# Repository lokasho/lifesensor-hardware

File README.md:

# lifesensor-hardware
Temporary repository for the next hardware generation of the CADUS Life Sensor.
Official repository at https://github.com/cadus/Life-Sensor.

## Similar projects and Resources:
- https://github.com/GliaX
- https://github.com/kitspace/awesome-electronics
- https://github.com/kitspace/kicad_footprints
- https://github.com/intajay/open-electronics

- ecg
    + https://github.com/xdever/MobilECG-II -> based on ADS1298
    + https://www.olimex.com/Products/Duino/Shields/SHIELD-EKG-EMG/open-source-hardware
    + https://www.electronicdesign.com/power-management/article/21798161/choose-the-right-resistors-for-medical-applications

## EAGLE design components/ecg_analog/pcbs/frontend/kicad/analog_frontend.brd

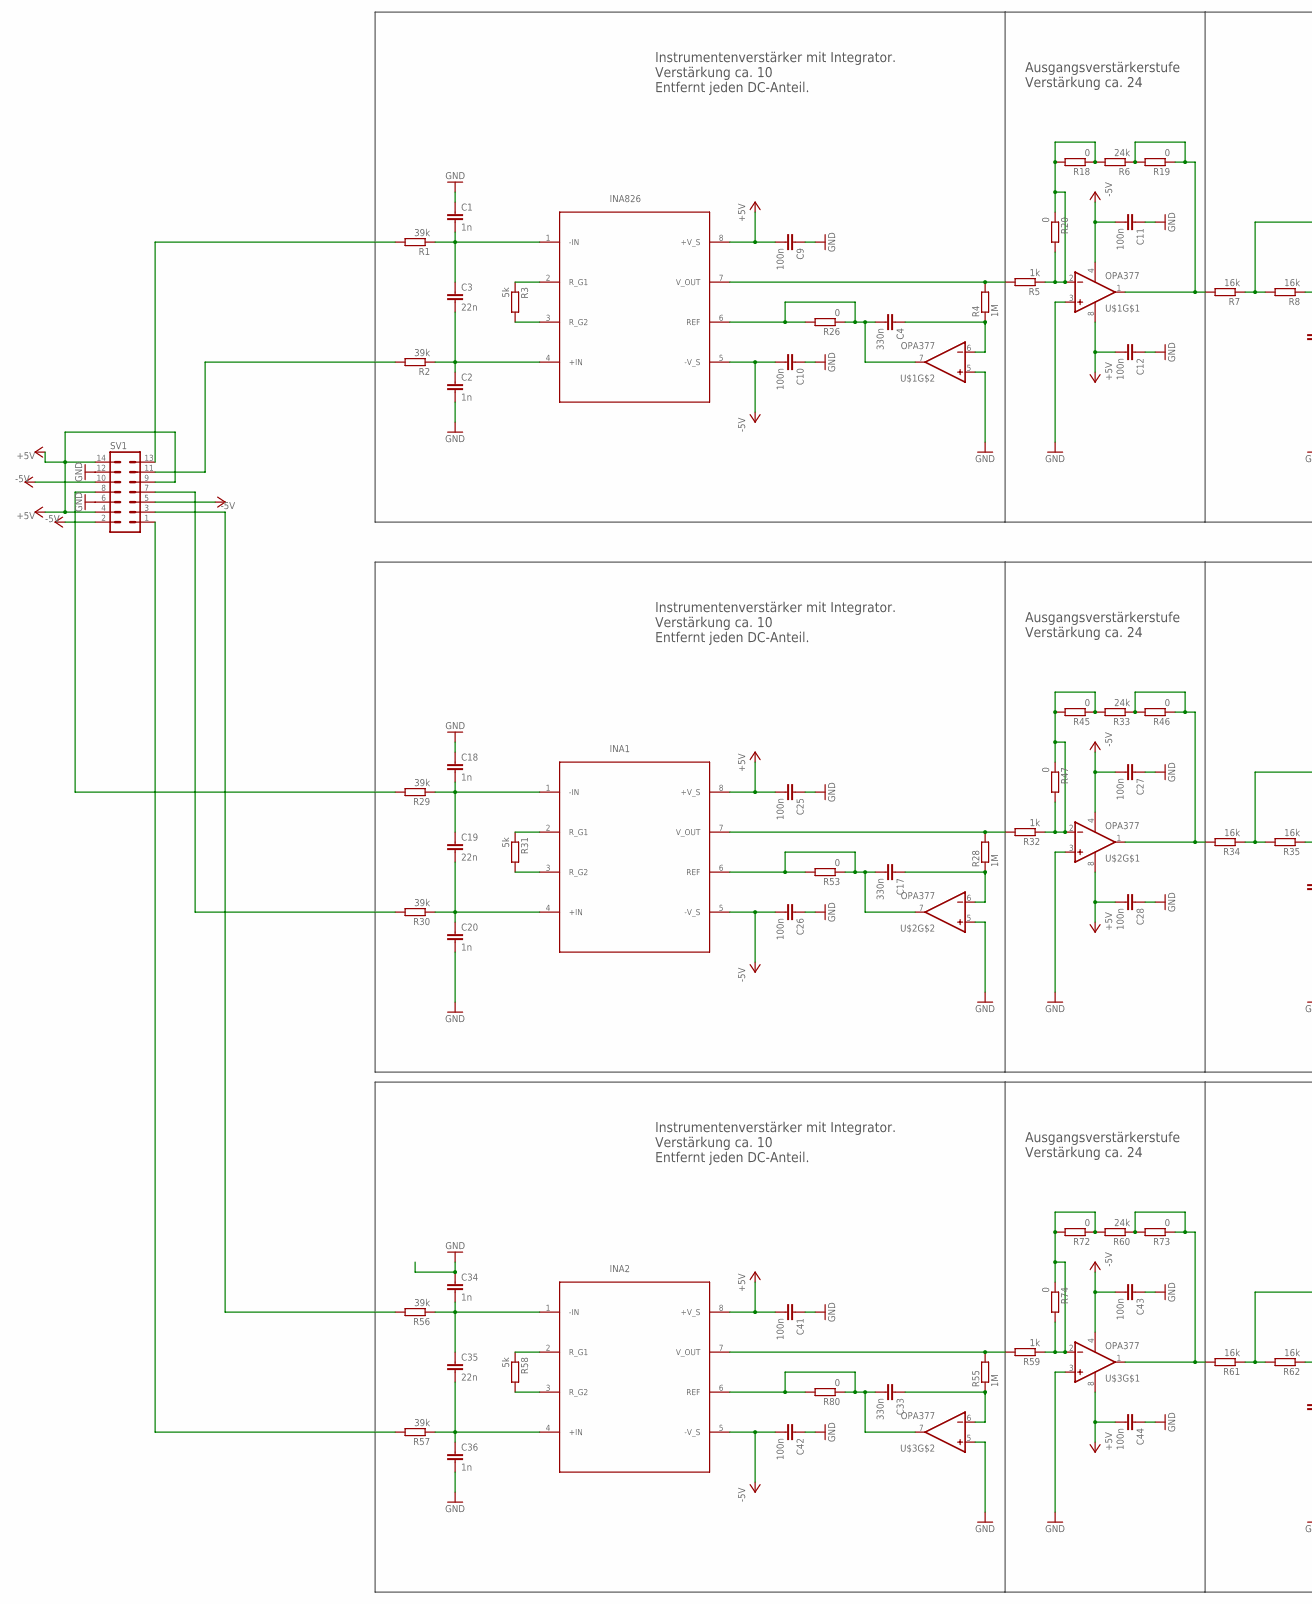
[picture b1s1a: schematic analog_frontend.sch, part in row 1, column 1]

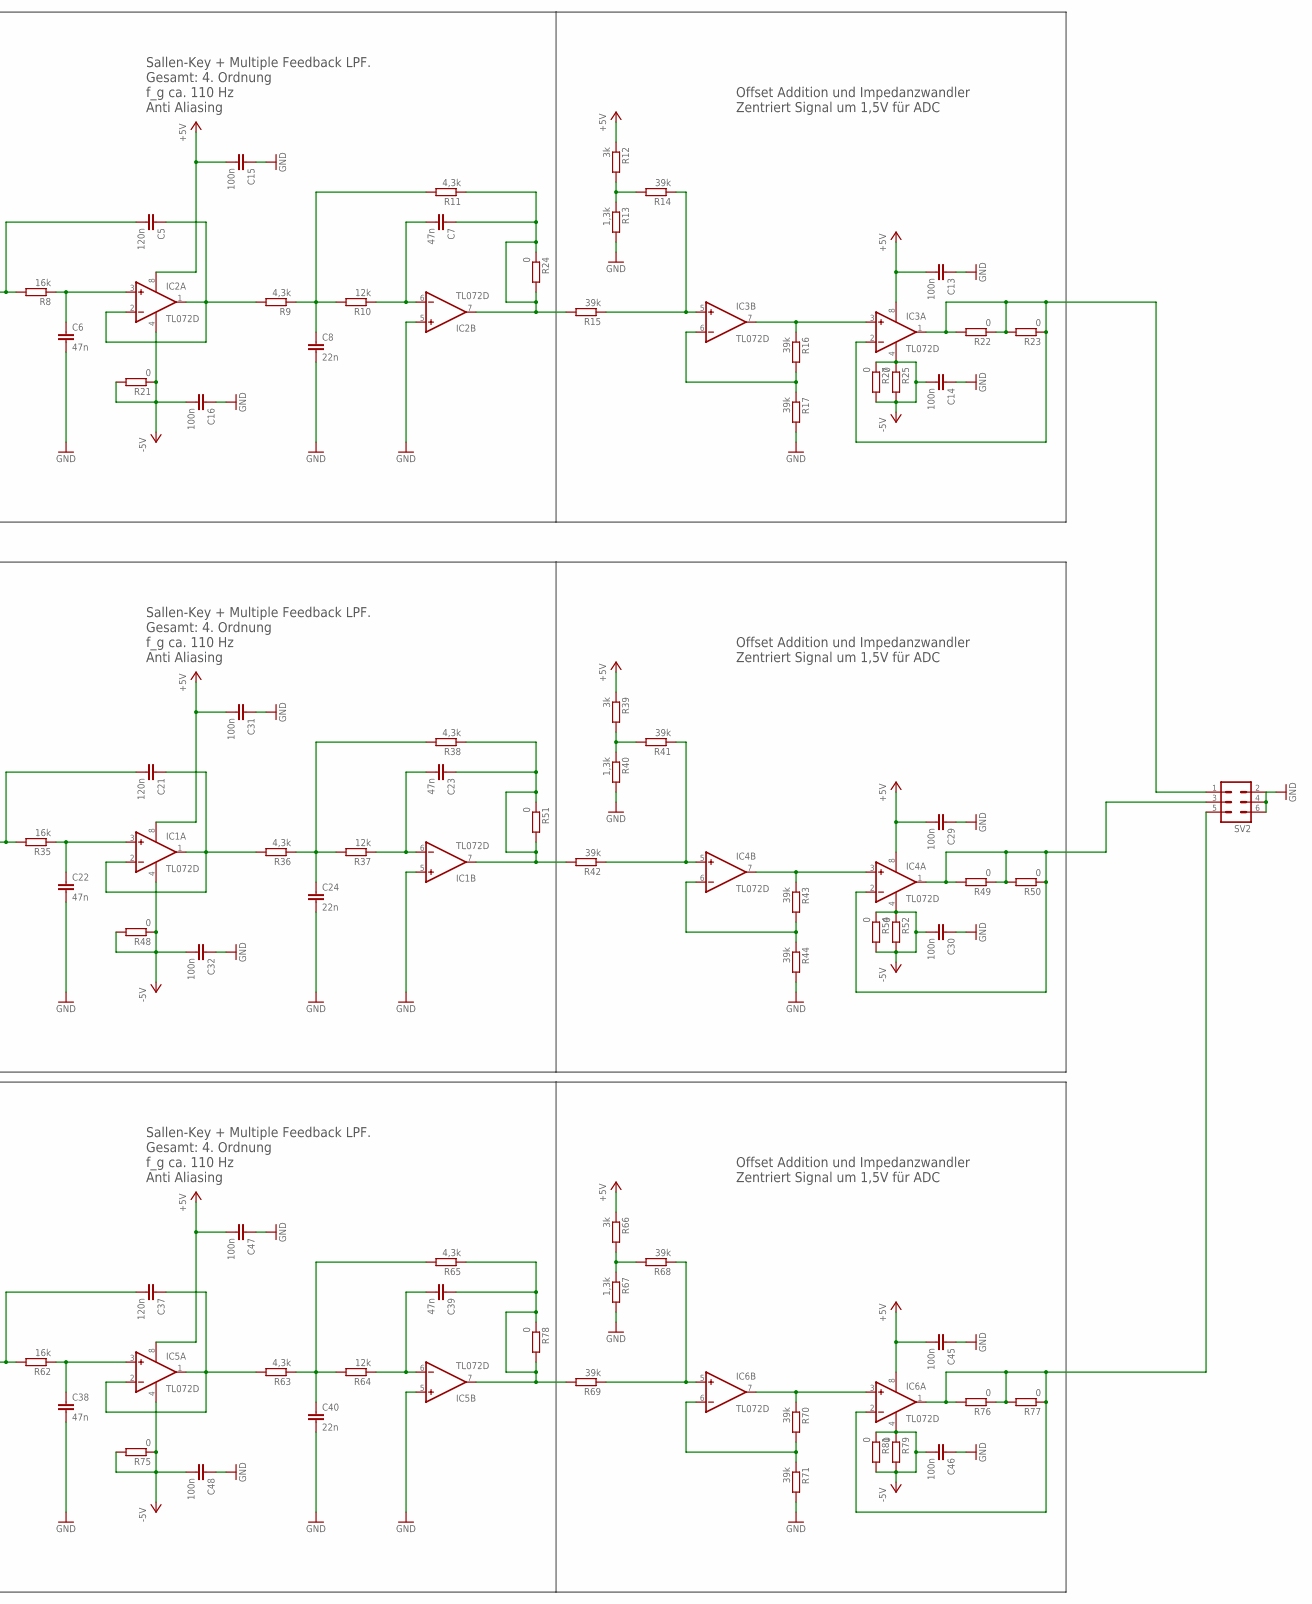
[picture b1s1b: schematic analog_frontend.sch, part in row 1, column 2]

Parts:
C1, C2, C18, C20, C34, C36: 1n; C0805
C3, C8, C19, C24, C35, C40: 22n; C0805
C4, C17, C33: 330n; C1206
C5, C21, C37: 120n; C0805
C6, C7, C22, C23, C38, C39: 47n; C0805
C9, C10, C11, C12, C13, C14, C16, C25, C26, C27, C28, C29, C30, C32, C41, C42, C43, C44, C45, C46, C48: 100n; C0805
C15, C31, C47: 100n; C1206
IC1, IC2, IC3, IC4, IC5, IC6: TL072D; SO08
INA1, INA2, INA826: INA826; SOIC8
R1, R2, R14, R15, R16, R29, R30, R41, R42, R43, R56, R57, R68, R69, R70: 39k; R0805
R3, R31, R58: 5k; R0805
R4, R28, R55: 1M; R1206
R5, R32, R59: 1k; R1206
R6, R33, R60: 24k; R0805
R7, R34, R61: 16k; R1206
R8, R35, R62: 16k; R0805
R9, R11, R36, R38, R63, R65: 4,3k; R0805
R10, R37, R64: 12k; R0805
R12, R39, R66: 3k; R0805
R13, R40, R67: 1,3k; R1206
R17, R44, R71: 39k; R1206
R18, R19, R20, R21, R22, R23, R24, R25, R26, R27, R45, R46, R47, R48, R49, R50, R51, R52, R53, R54, R72, R73, R74, R75, R76, R77, R78, R79, R80, R81: 0; R1206
SV1: ML14L
SV2: ML6L
U$1, U$2, U$3: OPA377; SOIC8

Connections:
+5V: C9.2, C12.2, C13.2, C15.2, C25.2, C28.2, C29.2, C31.2, C41.2, C44.2, C45.2, C47.2, IC1.8 (V+), IC2.8 (V+), IC3.8 (V+), IC4.8 (V+), IC5.8 (V+), IC6.8 (V+), INA1.8 (+V_S), INA2.8 (+V_S), INA826.8 (+V_S), R12.1, R39.1, R66.1, SV1.4, SV1.9, SV1.14, U$1.8 (V+), U$2.8 (V+), U$3.8 (V+)
-5V: C10.2, C11.2, C14.2, C16.2, C26.2, C27.2, C30.2, C32.2, C42.2, C43.2, C46.2, C48.2, IC1.4 (V-), IC2.4 (V-), IC3.4 (V-), IC4.4 (V-), IC5.4 (V-), IC6.4 (V-), INA1.5 (-V_S), INA2.5 (-V_S), INA826.5 (-V_S), R21.1, R21.2, R25.1, R25.2, R27.1, R27.2, R48.1, R48.2, R52.1, R52.2, R54.1, R54.2, R75.1, R75.2, R79.1, R79.2, R81.1, R81.2, SV1.2, SV1.5, SV1.10, U$1.4 (V-), U$2.4 (V-), U$3.4 (V-)
GND: C1.1, C2.2, C6.2, C8.2, C9.1, C10.1, C11.1, C12.1, C13.1, C14.1, C15.1, C16.1, C18.1, C20.2, C22.2, C24.2, C25.1, C26.1, C27.1, C28.1, C29.1, C30.1, C31.1, C32.1, C34.1, C36.2, C38.2, C40.2, C41.1, C42.1, C43.1, C44.1, C45.1, C46.1, C47.1, C48.1, IC1.5 (+IN), IC2.5 (+IN), IC5.5 (+IN), R13.2, R17.2, R40.2, R44.2, R67.2, R71.2, SV1.6, SV1.12, SV2.2, SV2.4, SV2.6, U$1.3 (+IN), U$1.5 (+IN), U$2.3 (+IN), U$2.5 (+IN), U$3.3 (+IN), U$3.5 (+IN)
unnamed: C4.2, INA826.6 (REF), R26.1, R26.2, U$1.7 (OUT)
unnamed: C4.1, R4.1, U$1.6 (-IN)
unnamed: INA826.7 (V_OUT), R4.2, R5.2
unnamed: C1.2, C3.1, INA826.1 (-IN), R1.1
unnamed: C2.1, C3.2, INA826.4 (+IN), R2.1
unnamed: INA826.3 (R_G2), R3.2
unnamed: INA826.2 (R_G1), R3.1
unnamed: R5.1, R6.2, R18.1, R18.2, R20.1, R20.2, U$1.2 (-IN)
unnamed: R6.1, R7.2, R19.1, R19.2, U$1.1 (OUT)
unnamed: C5.2, R7.1, R8.2
unnamed: C5.1, IC2.1 (OUT), IC2.2 (-IN), R9.2
unnamed: C6.1, IC2.3 (+IN), R8.1
unnamed: C8.1, R9.1, R10.2, R11.2
unnamed: C7.2, IC2.6 (-IN), R10.1
unnamed: C7.1, IC2.7 (OUT), R11.1, R15.2, R24.1, R24.2
unnamed: IC3.5 (+IN), R14.1, R15.1
unnamed: IC3.6 (-IN), R16.2, R17.1
unnamed: R12.2, R13.1, R14.2
unnamed: IC3.3 (+IN), IC3.7 (OUT), R16.1
unnamed: IC3.1 (OUT), IC3.2 (-IN), R22.1, R22.2, R23.1, R23.2, SV2.1
unnamed: R1.2, SV1.13
unnamed: R2.2, SV1.11
unnamed: INA1.7 (V_OUT), R28.2, R32.2
unnamed: C17.1, R28.1, U$2.6 (-IN)
unnamed: C18.2, C19.1, INA1.1 (-IN), R29.1
unnamed: C19.2, C20.1, INA1.4 (+IN), R30.1
unnamed: INA1.3 (R_G2), R31.2
unnamed: INA1.2 (R_G1), R31.1
unnamed: C21.2, R34.1, R35.2
unnamed: C21.1, IC1.1 (OUT), IC1.2 (-IN), R36.2
unnamed: C22.1, IC1.3 (+IN), R35.1
unnamed: C24.1, R36.1, R37.2, R38.2
unnamed: C23.2, IC1.6 (-IN), R37.1
unnamed: C23.1, IC1.7 (OUT), R38.1, R42.2, R51.1, R51.2
unnamed: IC4.5 (+IN), R41.1, R42.1
unnamed: R39.2, R40.1, R41.2
unnamed: IC4.3 (+IN), IC4.7 (OUT), R43.1
unnamed: IC4.6 (-IN), R43.2, R44.1
unnamed: R32.1, R33.2, R45.1, R45.2, R47.1, R47.2, U$2.2 (-IN)
unnamed: IC4.1 (OUT), IC4.2 (-IN), R49.1, R49.2, R50.1, R50.2, SV2.3
unnamed: C17.2, INA1.6 (REF), R53.1, R53.2, U$2.7 (OUT)
unnamed: R33.1, R34.2, R46.1, R46.2, U$2.1 (OUT)
unnamed: R29.2, SV1.8
unnamed: R30.2, SV1.7
unnamed: INA2.7 (V_OUT), R55.2, R59.2
unnamed: C33.1, R55.1, U$3.6 (-IN)
unnamed: C34.2, C35.1, INA2.1 (-IN), R56.1
unnamed: C35.2, C36.1, INA2.4 (+IN), R57.1
unnamed: INA2.3 (R_G2), R58.2
unnamed: INA2.2 (R_G1), R58.1
unnamed: C37.2, R61.1, R62.2
unnamed: C37.1, IC5.1 (OUT), IC5.2 (-IN), R63.2
unnamed: C38.1, IC5.3 (+IN), R62.1
unnamed: C40.1, R63.1, R64.2, R65.2
unnamed: C39.2, IC5.6 (-IN), R64.1
unnamed: C39.1, IC5.7 (OUT), R65.1, R69.2, R78.1, R78.2
unnamed: IC6.5 (+IN), R68.1, R69.1
unnamed: R66.2, R67.1, R68.2
unnamed: IC6.3 (+IN), IC6.7 (OUT), R70.1
unnamed: IC6.6 (-IN), R70.2, R71.1
unnamed: R59.1, R60.2, R72.1, R72.2, R74.1, R74.2, U$3.2 (-IN)
unnamed: IC6.1 (OUT), IC6.2 (-IN), R76.1, R76.2, R77.1, R77.2, SV2.5
unnamed: C33.2, INA2.6 (REF), R80.1, R80.2, U$3.7 (OUT)
unnamed: R60.1, R61.2, R73.1, R73.2, U$3.1 (OUT)
unnamed: R56.2, SV1.3
unnamed: R57.2, SV1.1

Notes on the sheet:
Instrumentenverstärker mit Integrator. Verstärkung ca. 10 Entfernt jeden DC-Anteil.
Ausgangsverstärkerstufe Verstärkung ca. 24
Sallen-Key + Multiple Feedback LPF. Gesamt: 4. Ordnung f_g ca. 110 Hz Anti Aliasing
Offset Addition und Impedanzwandler Zentriert Signal um 1,5V für ADC

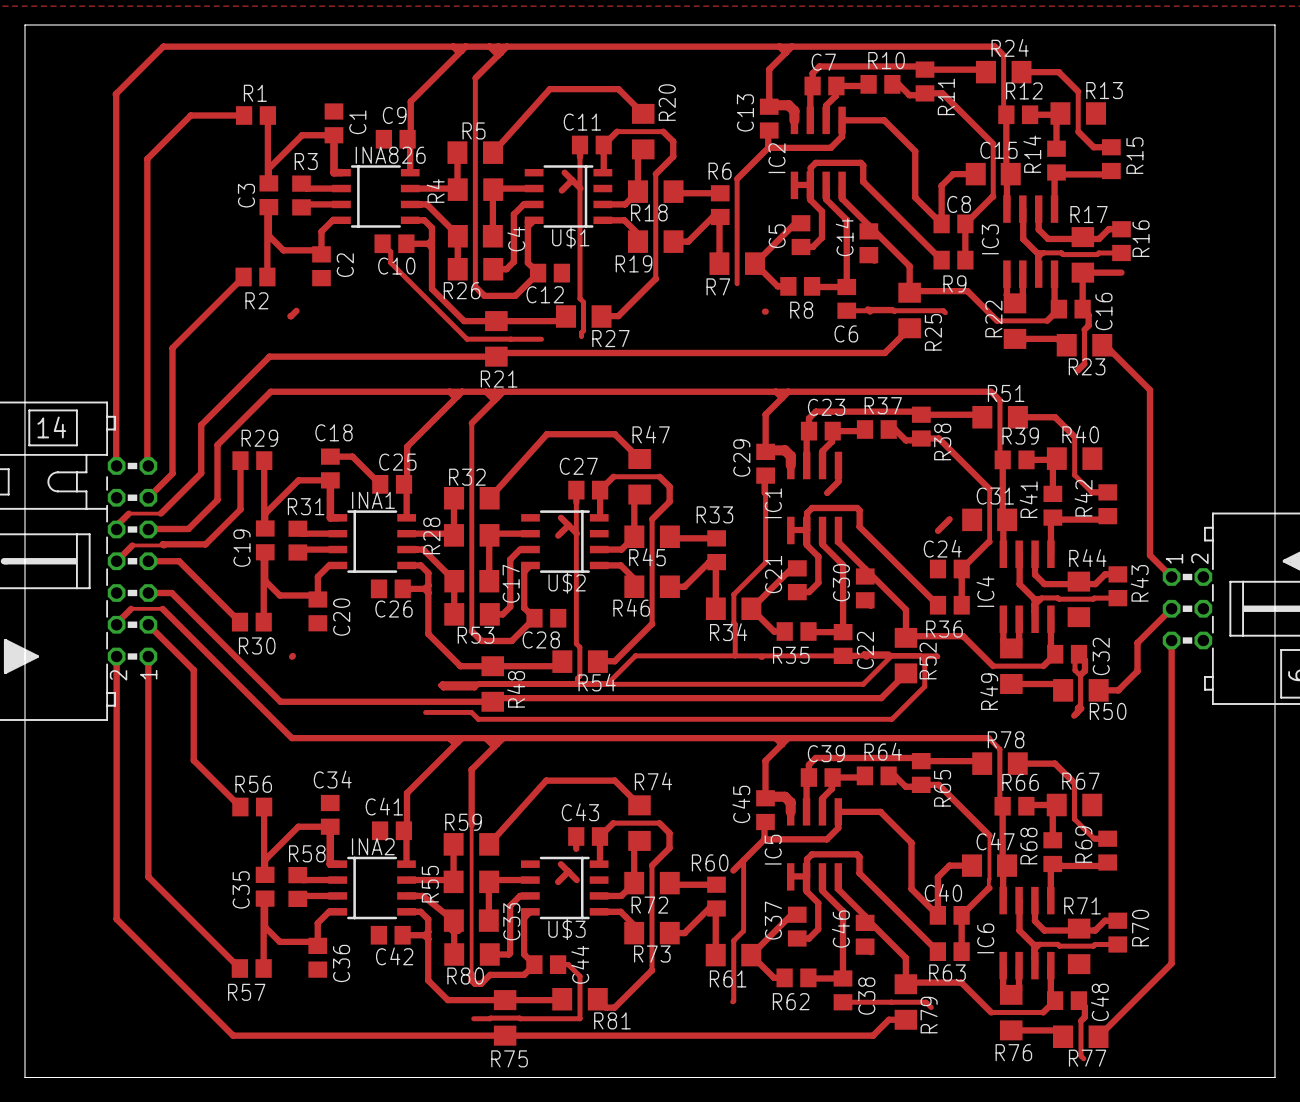
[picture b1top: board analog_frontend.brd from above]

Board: 2 copper layers, 100.0 x 84.2 mm, 143 parts (0 on the bottom side), 69 nets.

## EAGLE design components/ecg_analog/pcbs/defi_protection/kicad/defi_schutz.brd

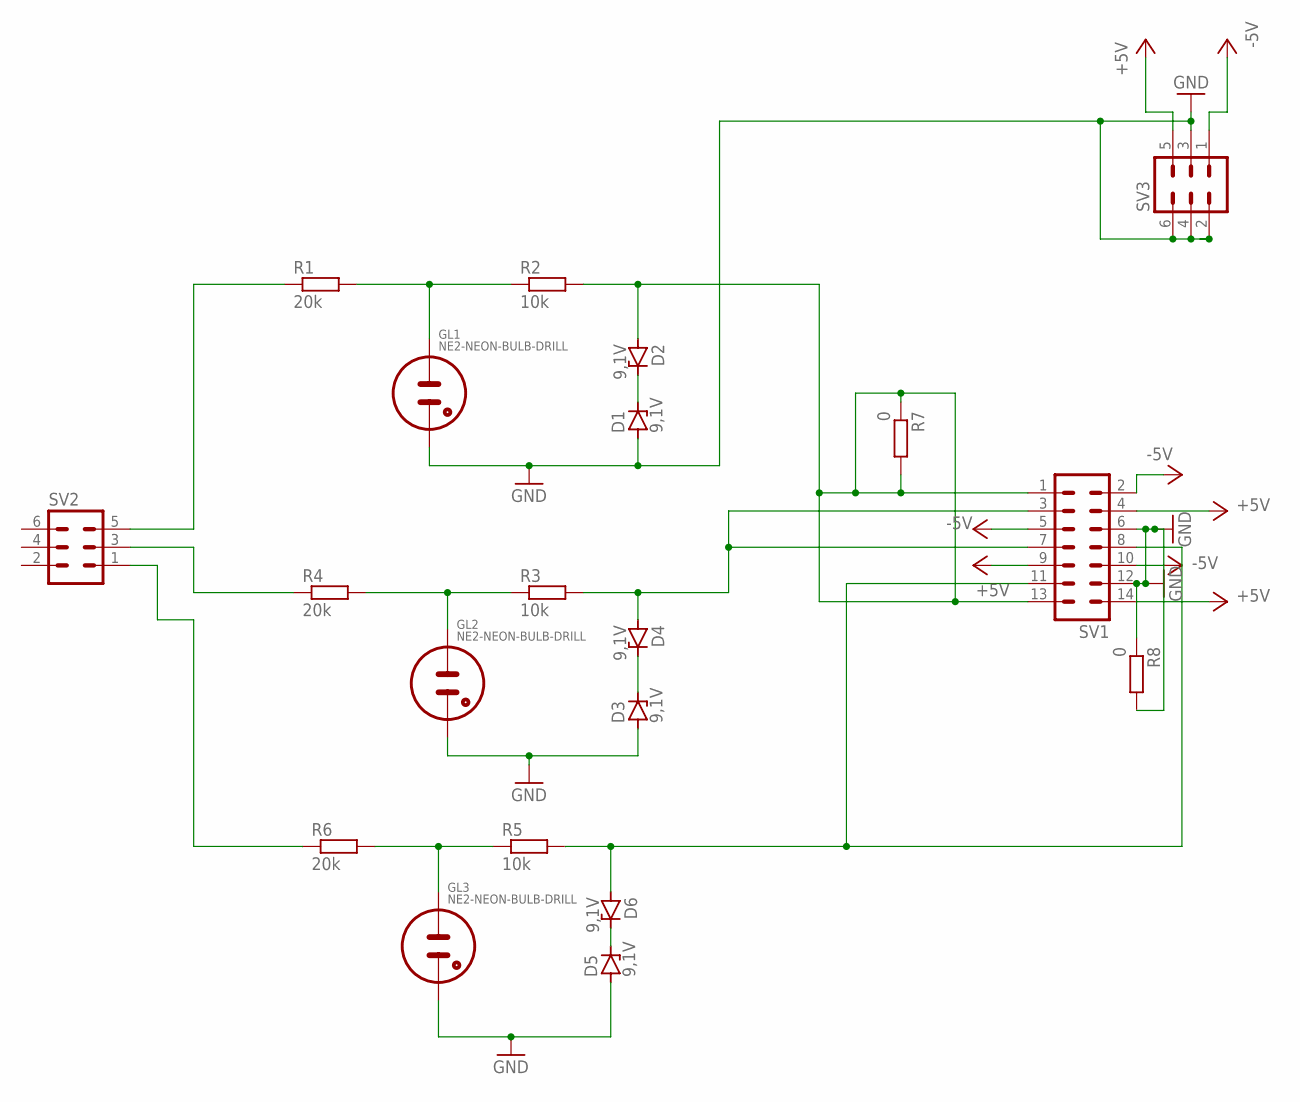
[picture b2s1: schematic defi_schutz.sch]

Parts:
D1, D2, D3, D4, D5, D6: 9,1V; DO41Z10
GL1, GL2, GL3: NE2-NEON-BULB-DRILL
R1, R4, R6: 20k; 0207/10
R2, R3, R5: 10k; 0207/10
R7, R8: 0; 0207/15
SV1: ML14L
SV2, SV3: ML6L

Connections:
+5V: SV1.4, SV1.9, SV1.14, SV3.5
-5V: SV1.2, SV1.5, SV1.10, SV3.1
GND: D1.A, D3.A, D5.A, GL1.2 (A1), GL2.2 (A1), GL3.2 (A1), R8.1, R8.2, SV1.6, SV1.12, SV3.2, SV3.3, SV3.4, SV3.6
unnamed: GL2.1 (A), R3.1, R4.2
unnamed: D4.A, R3.2, SV1.3, SV1.7
unnamed: D3.C, D4.C
unnamed: D1.C, D2.C
unnamed: GL1.1 (A), R1.2, R2.1
unnamed: D2.A, R2.2, R7.1, R7.2, SV1.1, SV1.13
unnamed: GL3.1 (A), R5.1, R6.2
unnamed: D6.A, R5.2, SV1.8, SV1.11
unnamed: D5.C, D6.C
unnamed: R1.1, SV2.5
unnamed: R4.1, SV2.3
unnamed: R6.1, SV2.1

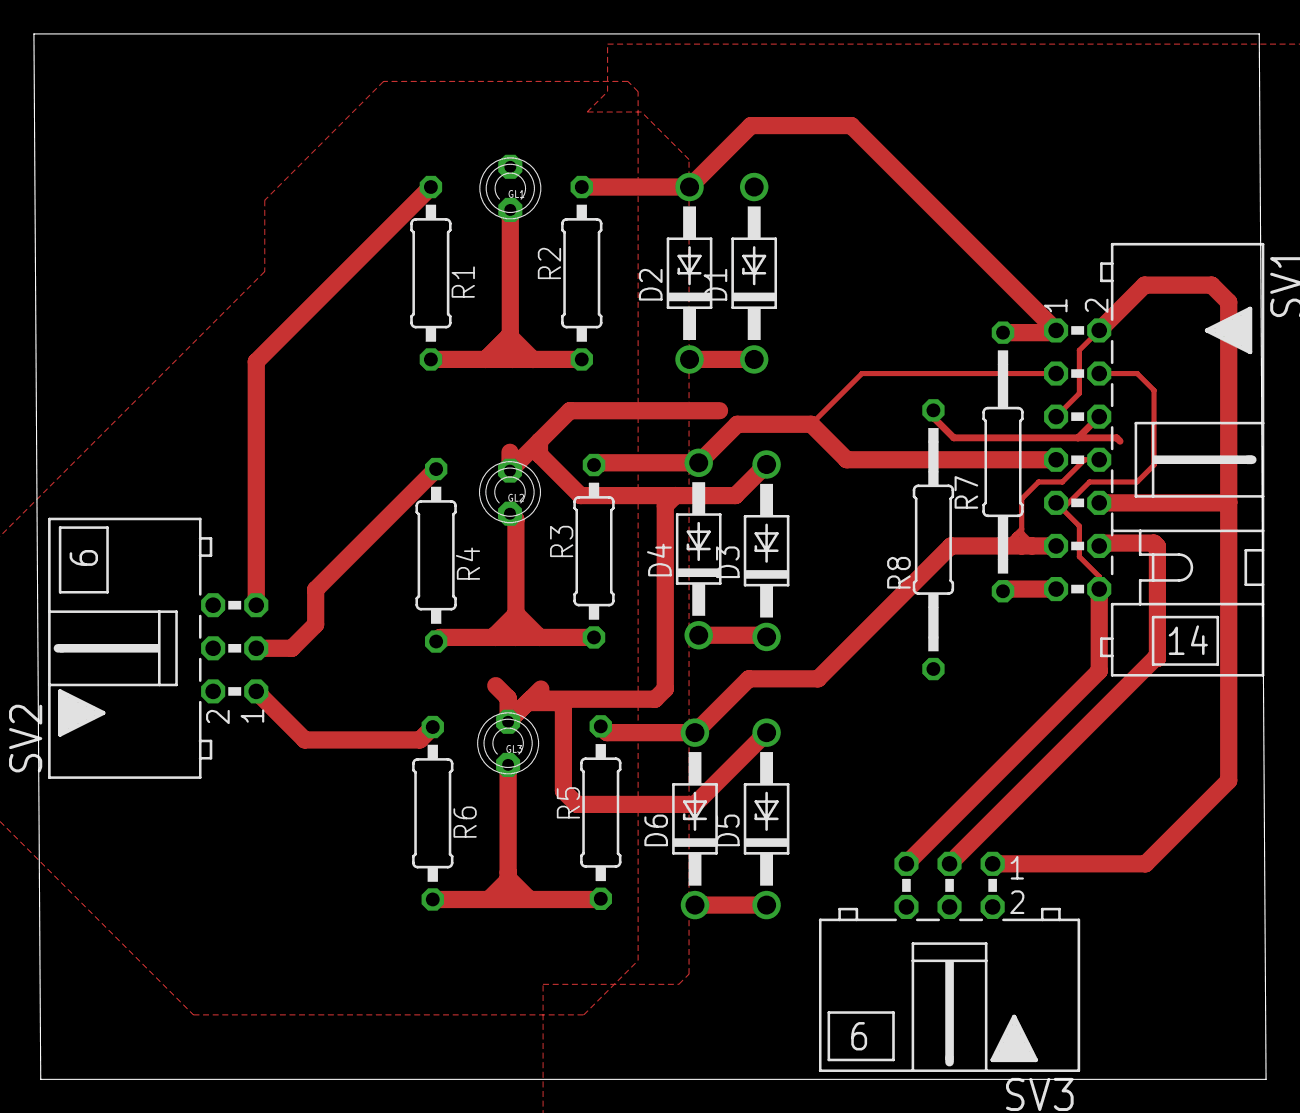
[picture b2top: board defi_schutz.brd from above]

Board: 2 copper layers, 72.6 x 61.6 mm, 20 parts (0 on the bottom side), 15 nets.

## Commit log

2020-03-26 add zenit resources
2020-03-27 update requirements
2020-03-27 add kicad project for ecg
2020-03-28 first draft ecg protection
2020-04-03 update file structure
2020-04-03 include analog frontend
2020-04-03 remove old ecg version
2020-04-03 add dummy ads1292 driver
2020-04-03 add dummy script
2020-04-07 update schematics
2020-04-11 allow daisy chaining and improve ground planes
2020-04-11 fix GND via not connected
2020-04-11 simplify ads1292 supply scheme in schematic
2020-04-15 orientation of pin headers in schematic matches pcb
2020-04-15 add gnd/gndpwr bridge at analog power supply
2020-04-15 add ERC log with allowed warnings
2020-04-15 add board name and version to pcb
2020-04-15 add version and titles to schematic pages
2020-04-22 first sim test with ne2 lib, blanks in sheet name removed
2020-04-25 updates simulation, adds diode, updates voltage source
2020-04-25 add system overview and pcb stack dimensions
2020-04-26 add templates for components and pcbs
2020-04-26 remove obsolete files
2020-04-26 allow scripts to be run from another working dir
2020-04-26 ignore python cache directories
2020-04-27 adds new tvs diode spice models
2020-04-27 new ecg_ads1292 version based on template
2020-04-27 update diode modell
2020-04-27 schematic passes erc with two accpted warnings
2020-04-27 schematic passes checklist
2020-04-27 the layout passes the checklist
2020-04-27 update check lists
2020-04-27 add gerber files
2020-04-27 add board svg image
2020-04-28 ignore schematic library cache in pcb template
2020-04-28 add chip select mux in pcb template
2020-04-28 add chip select mux in ads1292_main schematics
2020-04-28 add chip select mux on ads1292_main pcb
2020-04-28 update schematic check list
2020-04-29 fix project templates in pcb checklist
2020-04-29 better parameter name for lower_case_string function parameter
2020-05-07 add defiprotect_gdt component
2020-05-07 ecg_ads1292: fix symbol library paths
2020-05-07 add teardrops to layout
2020-05-07 ecg_ads1292 improve input filter circuit
2020-05-07 ecg_ads1292: improve power supply ferrit bead layout
2020-05-07 ecg_ads1292: remove obsolete pcb directory
2020-05-29 ecg_ads1292: update part fields
2020-05-31 ecg_ads1292: update schematic date
2020-05-31 ecg_ads1292: schematic checklist ok
2020-05-31 ecg_ads1292: layout checklist passed
2020-06-06 [WIP] ecg_ads1292: improve docs
2020-06-14 include board view svg instead of png in ads1292 README
2020-06-14 update parts and add digikey PNs
2020-06-14 add interactive BOM
2020-06-14 update parts in pcb
2020-06-18 add interconnect description
2020-06-18 update system overview
2020-06-20 remove outdated system overview png
2020-07-04 add ecg ads1292 pin/signal description to docs
2020-07-04 [WIP] adapt https://github.com/MitjaNemec/Kicad_action_plugins/blob/master/archive_project/archive_project.py
2020-07-07 move templates into common subdirectory
2020-07-07 use builtin __debug__ variable
2020-07-07 remove not used function parameters
2020-07-19 allow python version below 3.7
2020-07-19 remove old archive script
2020-07-19 add script to archive schematic symbols
2020-07-25 archive all components
2020-07-25 update docs
2020-08-25 add some tests
2020-08-25 improve pcb template
2020-08-25 board name defaults to None when creating a Settings object using python version below 3.7
2020-08-25 improve schematic check list
2020-08-25 create new component esp32_devkitc
2020-08-25 Add ESP32 DevKit-C symbol and footprint from snap eda
2020-08-25 add devkitc to board
2020-08-26 improve docs markdown templates
2020-08-26 ignore kicad symbol cache files
2020-08-26 adapt ecg_ads1292 docs to the template changes
2020-10-13 clean python scripts structure
2020-10-13 update interconnect
2020-10-13 add ESP32, WROOM32, DEVKIT-C data sheets
2020-10-13 [WIP] develop ESP32-main pcb
2020-10-13 add system overview to esp32 docs
2020-10-13 sackgasse1
2020-10-13 updates temp
2020-10-13 adds TODOs
2020-11-01 updates TODOs
2020-11-01 adds pinout table for devkitc
2020-11-01 updates pinout of esp32 devkitc, adds pinout odt document
2020-11-13 first drafted routing, WARNING: JTAG TCK missing!
2020-11-14 adds todos and notes
2020-11-22 Ready for review! fixes JTAG, adds updated pinout, updates JTAG header docu in Development_esp32_devkitc, finishes routing, adds JTAG resistors according to ESP32 manual
2020-11-24 small cleanup
2020-12-01 minorthing
2020-12-01 small update
2020-12-01 moves R21 below devkit
2020-12-01 Move FB1 closer to interconnect
2020-12-01 removes filling
2020-12-01 remove fillings for merge
2020-12-05 adds gpio expander, WIP
2020-12-05 updates 5V jack, adds jumpers for I2C GPIO Expander Adress, updates pinout, updates docs
2020-12-08 improve GND return paths for display SPI signals
